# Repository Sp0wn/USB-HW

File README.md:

# USB-HW
USB-HW is a simple USB to UART converter
with both the UART protocol and the RS-232 
protocols exposed in pin headers. It also
has some feature like ESD protection and
regulated 5 V and 3.3 V power buses.

## Schematic

## PCB

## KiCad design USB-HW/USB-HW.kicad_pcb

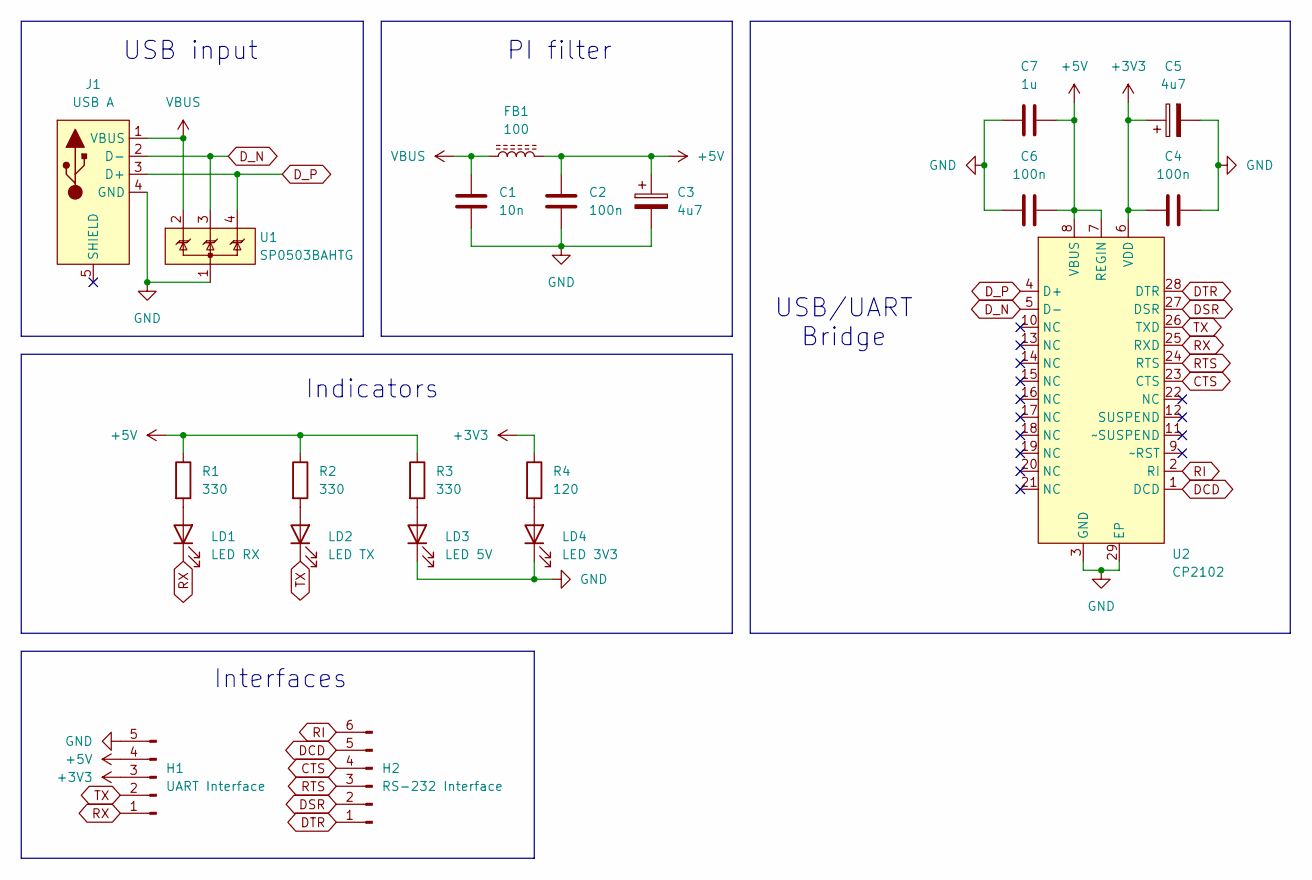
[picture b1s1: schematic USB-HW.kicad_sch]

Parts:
C1: 10n; C_0805_2012Metric
C2, C4, C6: 100n; C_0805_2012Metric
C3, C5: 4u7; CP_Elec_4x5.3
C7: 1u; C_0805_2012Metric
FB1: 100; L_0805_2012Metric
H1: UART Interface; PinHeader_1x05_P2.54mm_Vertical
H2: RS-232 Interface; PinSocket_1x06_P2.54mm_Vertical
J1: USB A; USB_A_Molex_48037-2200_Horizontal
LD1: LED RX; LED_0805_2012Metric
LD2: LED TX; LED_0805_2012Metric
LD3: LED 5V; LED_0805_2012Metric
LD4: LED 3V3; LED_0805_2012Metric
R1, R2, R3: 330; R_0805_2012Metric
R4: 120; R_0805_2012Metric
U1: SP0503BAHTG; SOT-143
U2: CP2102; QFN-28-1EP_5x5mm_P0.5mm_EP3.25x3.25mm

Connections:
+3V3: C4.2, C5.1, H1.3, R4.1, U2.6 (VDD)
+5V: C2.1, C3.1, C6.1, C7.1, FB1.2, H1.4, R1.1, R2.1, R3.1, U2.7 (REGIN), U2.8 (VBUS)
CTS: H2.4, U2.23 (CTS)
DCD: H2.5, U2.1 (DCD)
DSR: H2.2, U2.27 (DSR)
DTR: H2.1, U2.28 (DTR)
D_N: J1.2 (D-), U1.3 (I/O_2), U2.5 (D-)
D_P: J1.3 (D+), U1.4 (I/O_3), U2.4 (D+)
GND: C1.2, C2.2, C3.2, C4.1, C5.2, C6.2, C7.2, H1.5, J1.4 (GND), LD3.1 (K), LD4.1 (K), U1.1 (GND), U2.3 (GND), U2.29 (EP)
unnamed: LD1.2 (A), R1.2
unnamed: LD2.2 (A), R2.2
unnamed: LD3.2 (A), R3.2
unnamed: LD4.2 (A), R4.2
RI: H2.6, U2.2 (RI)
RTS: H2.3, U2.24 (RTS)
RX: H1.1, LD1.1 (K), U2.25 (RXD)
TX: H1.2, LD2.1 (K), U2.26 (TXD)
VBUS: C1.1, FB1.1, J1.1 (VBUS), U1.2 (I/O_1)

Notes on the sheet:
PI filter
USB input
Interfaces
USB/UART Bridge
Indicators

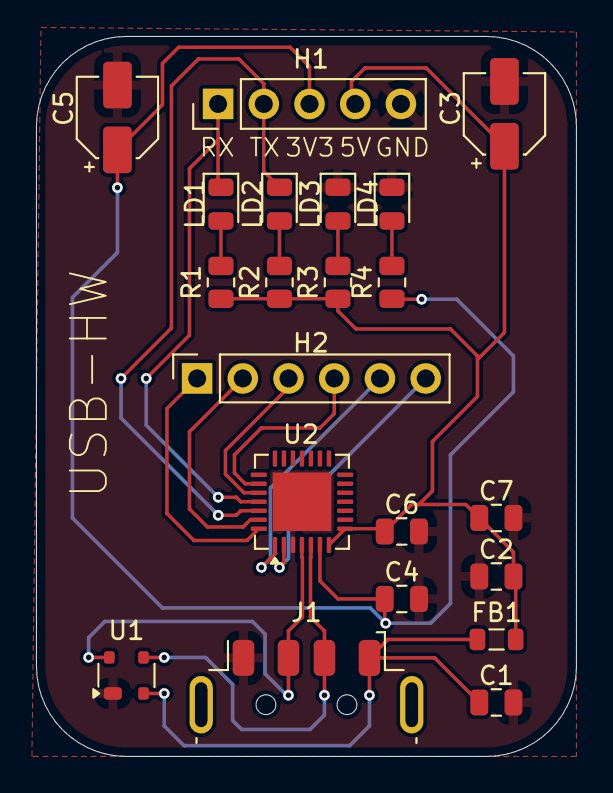
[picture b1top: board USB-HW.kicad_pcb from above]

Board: 2 copper layers, 30.0 x 40.0 mm, 21 parts (0 on the bottom side), 18 nets.

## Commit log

2025-12-29 Setup project
2025-12-30 feat: Add USB connector symbol
2026-01-01 feat: Add TVS array symbol
2026-01-02 feat: Add USB input section
2026-01-03 feat: Add CP2102 symbol
2026-01-05 feat: Add PI filter section
2026-01-05 feat: Add bridge section
2026-01-05 feat: Add indicators section
2026-01-05 feat: Add interfaces section
2026-01-14 feat: Add footprints
2026-01-14 feat: Add PCB
2026-01-14 feat: Add Images
